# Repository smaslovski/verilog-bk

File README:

This is a small and lightweigth VERILOG project that emulates some behavioral aspects
of the 1801BM1 CPU and the components found on the PCB of "-0011" (BK-0011M) computer.
BK-0011M was a popular PDP-compatible 16-bit home computer produced in the U.S.S.R. in 1980s.

The purpose of this project is to test extension circuits for this computer at early design stages.
Currently (June 12, 2020), only the code for the CPU bus write cycle is implemented in the CPU emulator,
and the only extensions being tested are 3 variants of AY-3-8910/YM2149 interface circuits.

Yes, I am well aware of the great projects put forward by Viacheslav (Slava) 1801BM1
(https://github.com/1801BM1/cpu11) and by lvd2 (https://github.com/lvd2/ay-3-8910_reverse_engineered),
but my point here is not to reinvent the weel, it is just to have fun!

It is possible that some of the modules from this project could be later included in other
verilog projects that deal with emulation of old computers (both in software and in hardware).

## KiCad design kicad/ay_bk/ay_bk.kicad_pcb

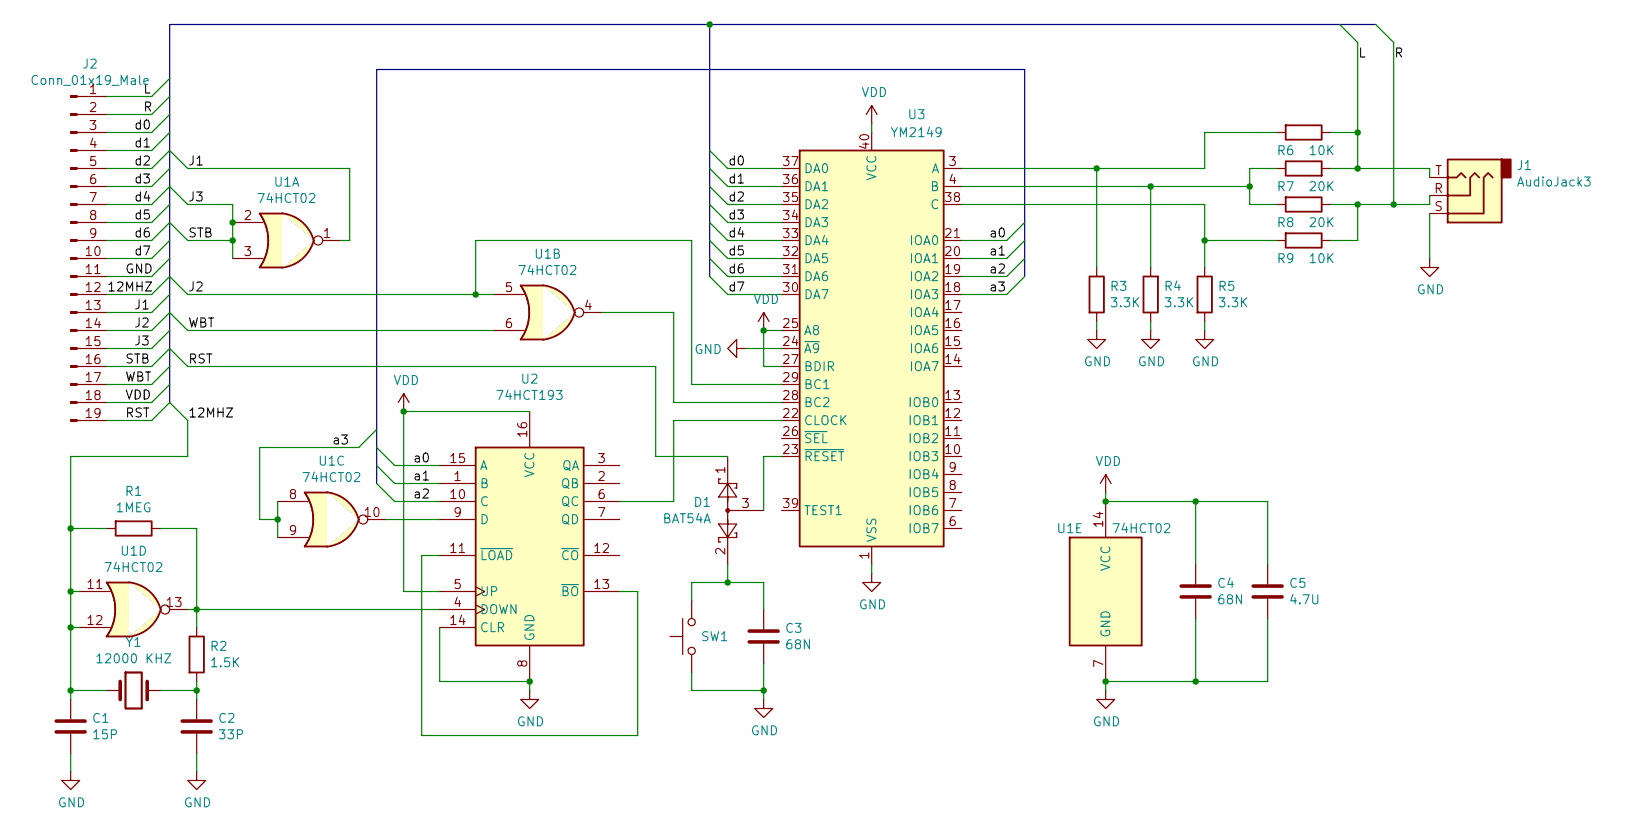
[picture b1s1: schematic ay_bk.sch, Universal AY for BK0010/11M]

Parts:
C1: 15P; C_1206_3216Metric_Pad1.33x1.80mm_HandSolder
C2: 33P; C_1206_3216Metric_Pad1.33x1.80mm_HandSolder
C3, C4: 68N; C_1210_3225Metric_Pad1.33x2.70mm_HandSolder
C5: 4.7U; C_1210_3225Metric_Pad1.33x2.70mm_HandSolder
D1: BAT54A; SOT-23
J1: AudioJack3; Jack_3.5mm_CUI_SJ1-3535NG_Horizontal
J2: Conn_01x19_Male; PinHeader_1x19_P2.00mm_Vertical
R1: 1MEG; R_1206_3216Metric_Pad1.30x1.75mm_HandSolder
R2: 1.5K; R_1206_3216Metric_Pad1.30x1.75mm_HandSolder
R3, R4, R5: 3.3K; R_1206_3216Metric_Pad1.30x1.75mm_HandSolder
R6, R9: 10K; R_1206_3216Metric_Pad1.30x1.75mm_HandSolder
R7, R8: 20K; R_1206_3216Metric_Pad1.30x1.75mm_HandSolder
SW1: SW_Push; SW_SPST_PTS645
U1: 74HCT02; SOIC-14_3.9x8.7mm_P1.27mm
U2: 74HCT193; SOIC-16_3.9x9.9mm_P1.27mm
U3: YM2149; DIP-40_W15.24mm
Y1: 12000 KHZ; Crystal_HC49-U_Vertical

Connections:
/12MHZ: C1.1, J2.12, R1.2, U1.11, U1.12, Y1.1
/J1: J2.13, U1.1
/J2: J2.14, U1.5, U3.29 (BC1)
/J3: J2.15, J2.16, U1.2, U1.3
/L: J1.T, J2.1, R6.1, R7.2
/R: J1.R, J2.2, R8.1, R9.1
/RST: D1.1, J2.19
/WBT: J2.17, U1.6
/a0: U2.15 (A), U3.21 (IOA0)
/a1: U2.1 (B), U3.20 (IOA1)
/a2: U2.10 (C), U3.19 (IOA2)
/a3: U1.8, U1.9, U3.18 (IOA3)
/d0: J2.3, U3.37 (DA0)
/d1: J2.4, U3.36 (DA1)
/d2: J2.5, U3.35 (DA2)
/d3: J2.6, U3.34 (DA3)
/d4: J2.7, U3.33 (DA4)
/d5: J2.8, U3.32 (DA5)
/d6: J2.9, U3.31 (DA6)
/d7: J2.10, U3.30 (DA7)
GND: C1.2, C2.2, C3.2, C4.2, C5.2, J1.S, J2.11, R3.2, R4.1, R5.2, SW1.1, U1.7 (GND), U2.8 (GND), U2.14 (CLR), U3.1 (VSS), U3.24 (~A9)
unnamed: C2.1, R2.2, Y1.2
unnamed: C3.1, D1.2, SW1.2
unnamed: D1.3, U3.23 (~RESET)
unnamed: R1.1, R2.1, U1.13, U2.4 (DOWN)
unnamed: R3.1, R6.2, U3.3 (A)
unnamed: R4.2, R7.1, R8.2, U3.4 (B)
unnamed: R5.1, R9.2, U3.38 (C)
unnamed: U1.4, U3.28 (BC2)
unnamed: U1.10, U2.9 (D)
unnamed: U2.6 (QC), U3.22 (CLOCK)
unnamed: U2.11 (~LOAD), U2.13 (~BO)
VDD: C4.1, C5.1, J2.18, U1.14 (VCC), U2.5 (UP), U2.16 (VCC), U3.25 (A8), U3.27 (BDIR), U3.40 (VCC)

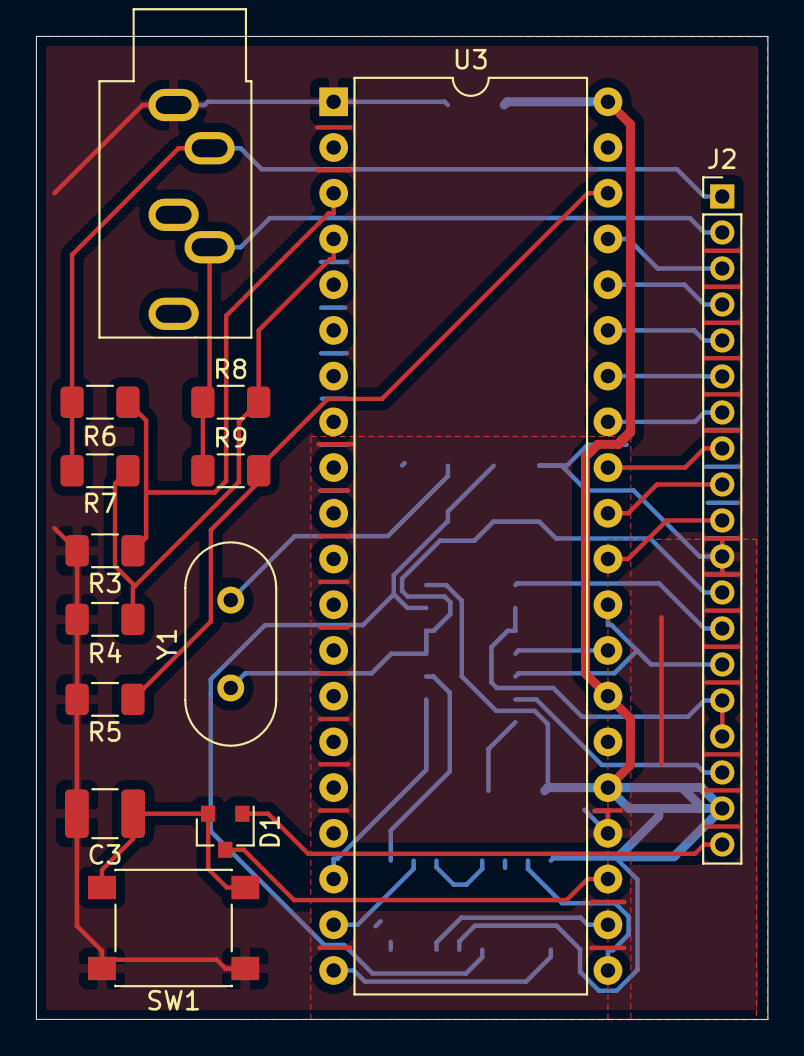
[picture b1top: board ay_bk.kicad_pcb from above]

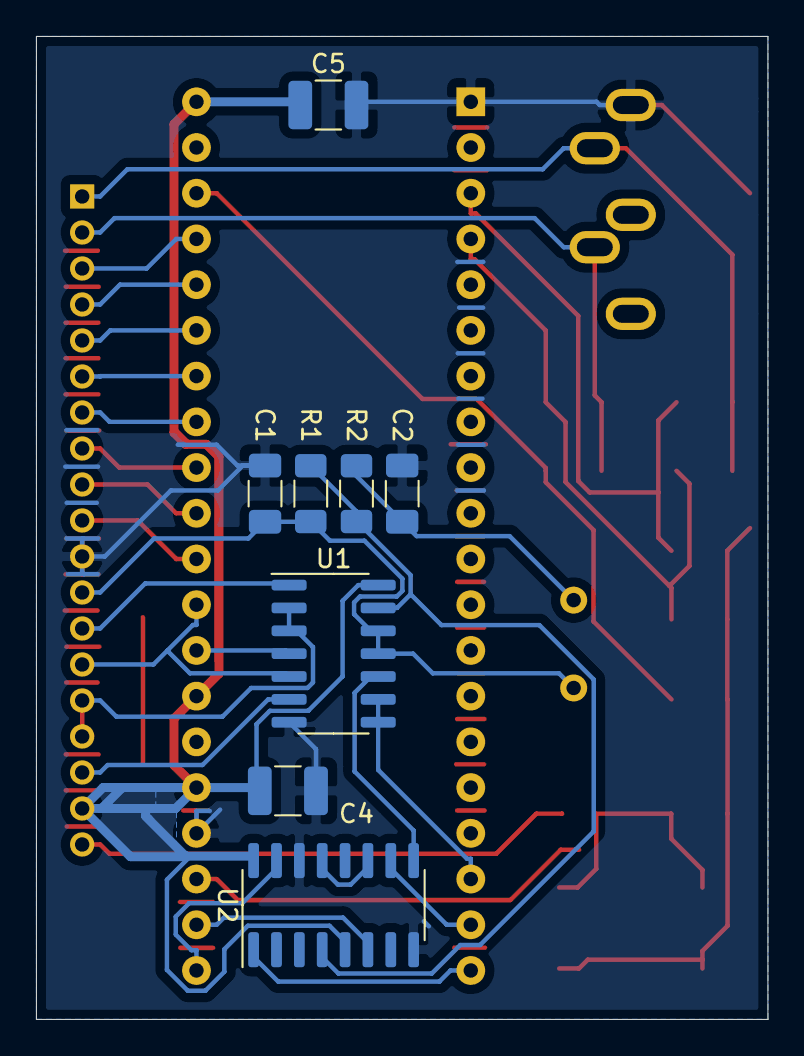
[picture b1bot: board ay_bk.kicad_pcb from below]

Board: 2 copper layers, 40.6 x 54.6 mm, 22 parts (8 on the bottom side), 33 nets.

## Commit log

2020-06-12 Add files via upload
    Add files in UTF-8 encoding.
2020-06-12 Update ay_cmd_test.v
    Fix misprint
2020-06-12 Fix misprint
2020-06-12 Fix .PHONY targets
2020-06-12 Revert "Fix .PHONY targets"
    This reverts commit fb46fef9b20f924fd69fa93c0948b7789112c346.
2020-06-12 Use blocking assignments in the clock generator.
2020-06-12 The AD bus is in an undefined state right after finishing the address cycle and before the actual data are ready to be sent. Emulate this.
2020-06-12 fix a misprint
2020-06-13 Add generating output to gtkwave
2020-06-13 Update clean target
2020-06-13 cleanup
2020-06-13 Restart on RPLY timeout
2020-06-16 Implement read bus cycle
2020-06-18 FSM rewrite
2020-06-21 Extend the state reg to 9 bits
2020-08-06 Add a test for -037
2020-08-06 remove old 5ns delay
2020-08-06 update Makefile
2021-04-05 Add kicad files
2021-04-09 improve reset circuit
2021-04-12 corect delay value; dump AY signals
2021-04-12 fix signal dumping
2021-04-12 add propagation delay for K555IR22
2021-06-18 Add 3rd variant
2021-06-18 fix delays
